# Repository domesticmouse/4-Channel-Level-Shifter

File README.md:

# 4-Channel Bidirectional Level Shifter

## Overview

This board is a 4-channel bidirectional logic level converter designed to safely
interface between different voltage domains (typically 3.3V and 5V). It is based
on the [Adafruit 4-channel I2C-safe Bi-directional Logic Level Converter][]. See
the [Adafruit learn documentation][] on converting
[I2C data lines between 3.3V and 5V][] for context on this circuit.

[Adafruit 4-channel I2C-safe Bi-directional Logic Level Converter]: https://www.adafruit.com/product/757
[Adafruit learn documentation]: https://learn.adafruit.com/
[I2C data lines between 3.3V and 5V]: https://learn.adafruit.com/introducing-adafruit-stemma-qt/technical-specs#data-lines-3035228

## Technical Specifications

- **Core Logic:** 4x [BSS138 N-channel MOSFETs][].
- **Pull-up Resistors:** 10kΩ on all input/output signal lines.
- **Voltage Range:**
  - **LV (Low Voltage):** Typically 1.8V to 3.3V.
  - **HV (High Voltage):** Typically up to 5V (limited by MOSFET Vgs/Vds).
- **Decoupling:** 100nF ceramic capacitors on both power rails for noise suppression.

[BSS138 N-channel MOSFETs]: https://www.lcsc.com/product-detail/C5224260.html

## Pinout

### J1 (High Voltage Side)

| Pin | Label | Description |
| --- | --- | --- |
| 1 | **5V** | High Voltage Power Rail (e.g., 5V) |
| 2 | **HV1** | Channel 1 High Side |
| 3 | **HV2** | Channel 2 High Side |
| 4 | **HV3** | Channel 3 High Side |
| 5 | **HV4** | Channel 4 High Side |
| 6 | **GND** | Ground |

### J2 (Low Voltage Side)

| Pin | Label | Description |
| --- | --- | --- |
| 1 | **3.3V** | Low Voltage Power Rail (e.g., 3.3V) |
| 2 | **LV1** | Channel 1 Low Side |
| 3 | **LV2** | Channel 2 Low Side |
| 4 | **LV3** | Channel 3 Low Side |
| 5 | **LV4** | Channel 4 Low Side |
| 6 | **GND** | Ground |

## PCB Features

- **Form Factor:** Approximately 18.8mm x 18.4mm.
- **Signal Integrity:** Solid ground planes on both layers with stitching vias.
- **Usability:** Silkscreen labeling for all channels and power pins.

## Usage Guide

1. **Power:** Connect your low-voltage supply to **3.3V** and your high-voltage supply to **5V**.
2. **Ground:** Connect **GND** to your common system ground.
3. **Logic:** Connect your 3.3V logic signals to the **LVn** pins; the corresponding **HVn** pins will provide the 5V shifted output (and vice-versa for bidirectional signals).

## Board render

---
*Developed as a KiCad 10 project.*

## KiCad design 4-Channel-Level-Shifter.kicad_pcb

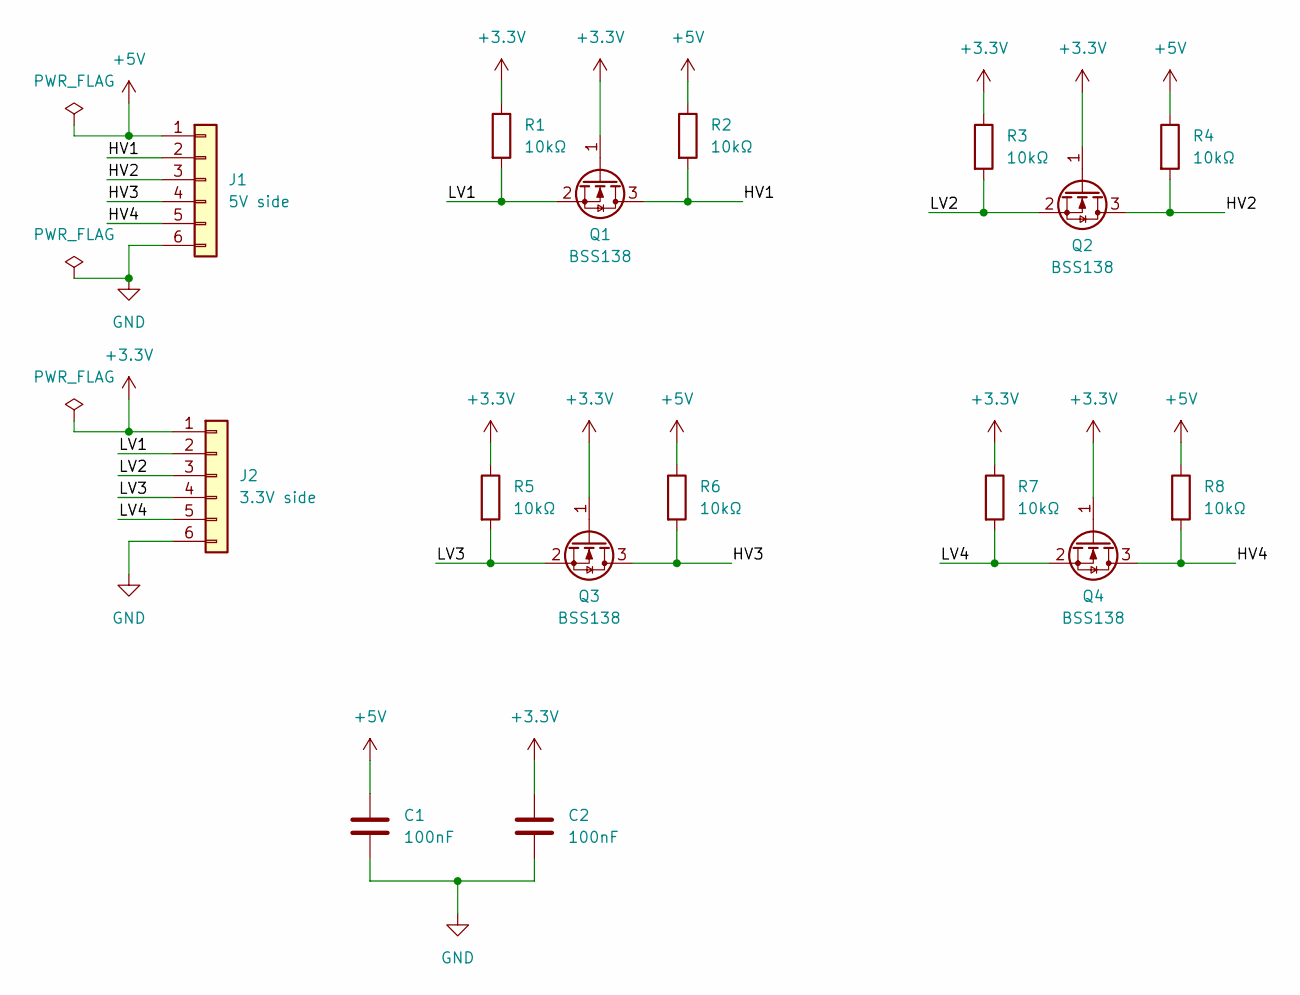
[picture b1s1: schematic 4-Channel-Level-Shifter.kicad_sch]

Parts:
C1, C2: 100nF; C_0603_1608Metric_Pad1.08x0.95mm_HandSolder; LCSC C14663
J1: 5V side; PinHeader_1x06_P2.54mm_Vertical; LCSC C37208
J2: 3.3V side; PinHeader_1x06_P2.54mm_Vertical; LCSC C37208
Q1, Q2, Q3, Q4: BSS138; SOT-23; LCSC C5224260
R1, R2, R3, R4, R5, R6, R7, R8: 10kΩ; R_0603_1608Metric_Pad0.98x0.95mm_HandSolder; LCSC C2906982

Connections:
+3.3V: C2.1, J2.1, Q1.1 (G), Q2.1 (G), Q3.1 (G), Q4.1 (G), R1.1, R3.1, R5.1, R7.1
+5V: C1.1, J1.1, R2.1, R4.1, R6.1, R8.1
/HV1: J1.2, Q1.3 (D), R2.2
/HV2: J1.3, Q2.3 (D), R4.2
/HV3: J1.4, Q3.3 (D), R6.2
/HV4: J1.5, Q4.3 (D), R8.2
/LV1: J2.2, Q1.2 (S), R1.2
/LV2: J2.3, Q2.2 (S), R3.2
/LV3: J2.4, Q3.2 (S), R5.2
/LV4: J2.5, Q4.2 (S), R7.2
GND: C1.2, C2.2, J1.6, J2.6

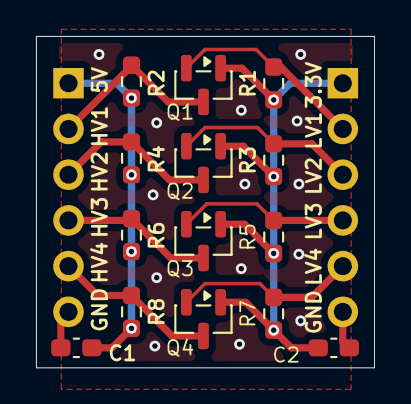
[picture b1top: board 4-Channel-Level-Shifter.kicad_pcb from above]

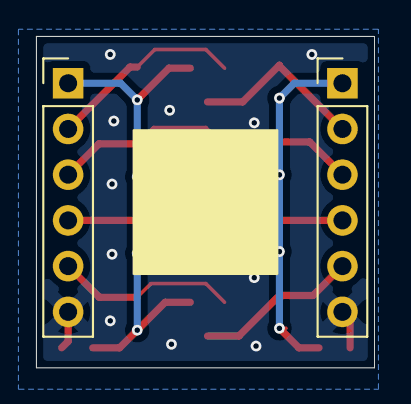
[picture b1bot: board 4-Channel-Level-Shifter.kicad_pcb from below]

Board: 2 copper layers, 18.8 x 18.4 mm, 16 parts (2 on the bottom side), 11 nets.

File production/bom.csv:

Designator,Footprint,Quantity,Value,LCSC Part #
"C1, C2",0603,2,100nF,C14663
J1,PinHeader_1x06_P2.54mm_Vertical,1,5V side,C37208
J2,PinHeader_1x06_P2.54mm_Vertical,1,3.3V side,C37208
"Q1, Q2, Q3, Q4",SOT-23,4,BSS138,C5224260
"R1, R2, R3, R4, R5, R6, R7, R8",0603,8,10kΩ,C2906982

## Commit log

2026-05-07 Update schematic
2026-05-07 Add production files
2026-05-07 Cleanup
2026-05-08 Add dimension between connectors
